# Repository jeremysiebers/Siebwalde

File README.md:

# Siebwalde-Source
Siebwalde project

This project is dedicated for the ModelTrain Yard of Siebwalde: 
- https://www.youtube.com/c/SiebersOrg
- http://www.siebers.org/index.html
- https://www.youtube.com/channel/UCRJYaY8l7wVBrel3Bn0nD2Q/videos?view_as=subscriber

It contains sources for:

Windows Application (C#)

- Siebwalde_Application     --> C# main App to control all

uCOntrollers (C):

- FiddleYard                --> Embedded ethernet uController, controlling the FiddleYard PIC18F97j60

- ServoController.X         --> Embedded uController for RC servo driving

- TrackAmplifier4.X         --> development of track amplifiers; 1 PIC per amplifier (final setup with PIC18F25K40)(PetitModbus)*

- TrackBackplane2.X         --> development of track backplane slave; track amplifier slave select slave for initialization (final setup with PIC18F25K40)(PetitModbus)*

- TrackController5.X        --> development of track controller; PIC32MZ2048EFH144 Ethernet Target + ModBus Master(build upon PetitModbus)*

PCB Files (KiCad):

- KiCad                     --> All Siebwalde related KiCad (PCB) designs

*PetitModbus derived from https://github.com/FxDev/PetitModbus

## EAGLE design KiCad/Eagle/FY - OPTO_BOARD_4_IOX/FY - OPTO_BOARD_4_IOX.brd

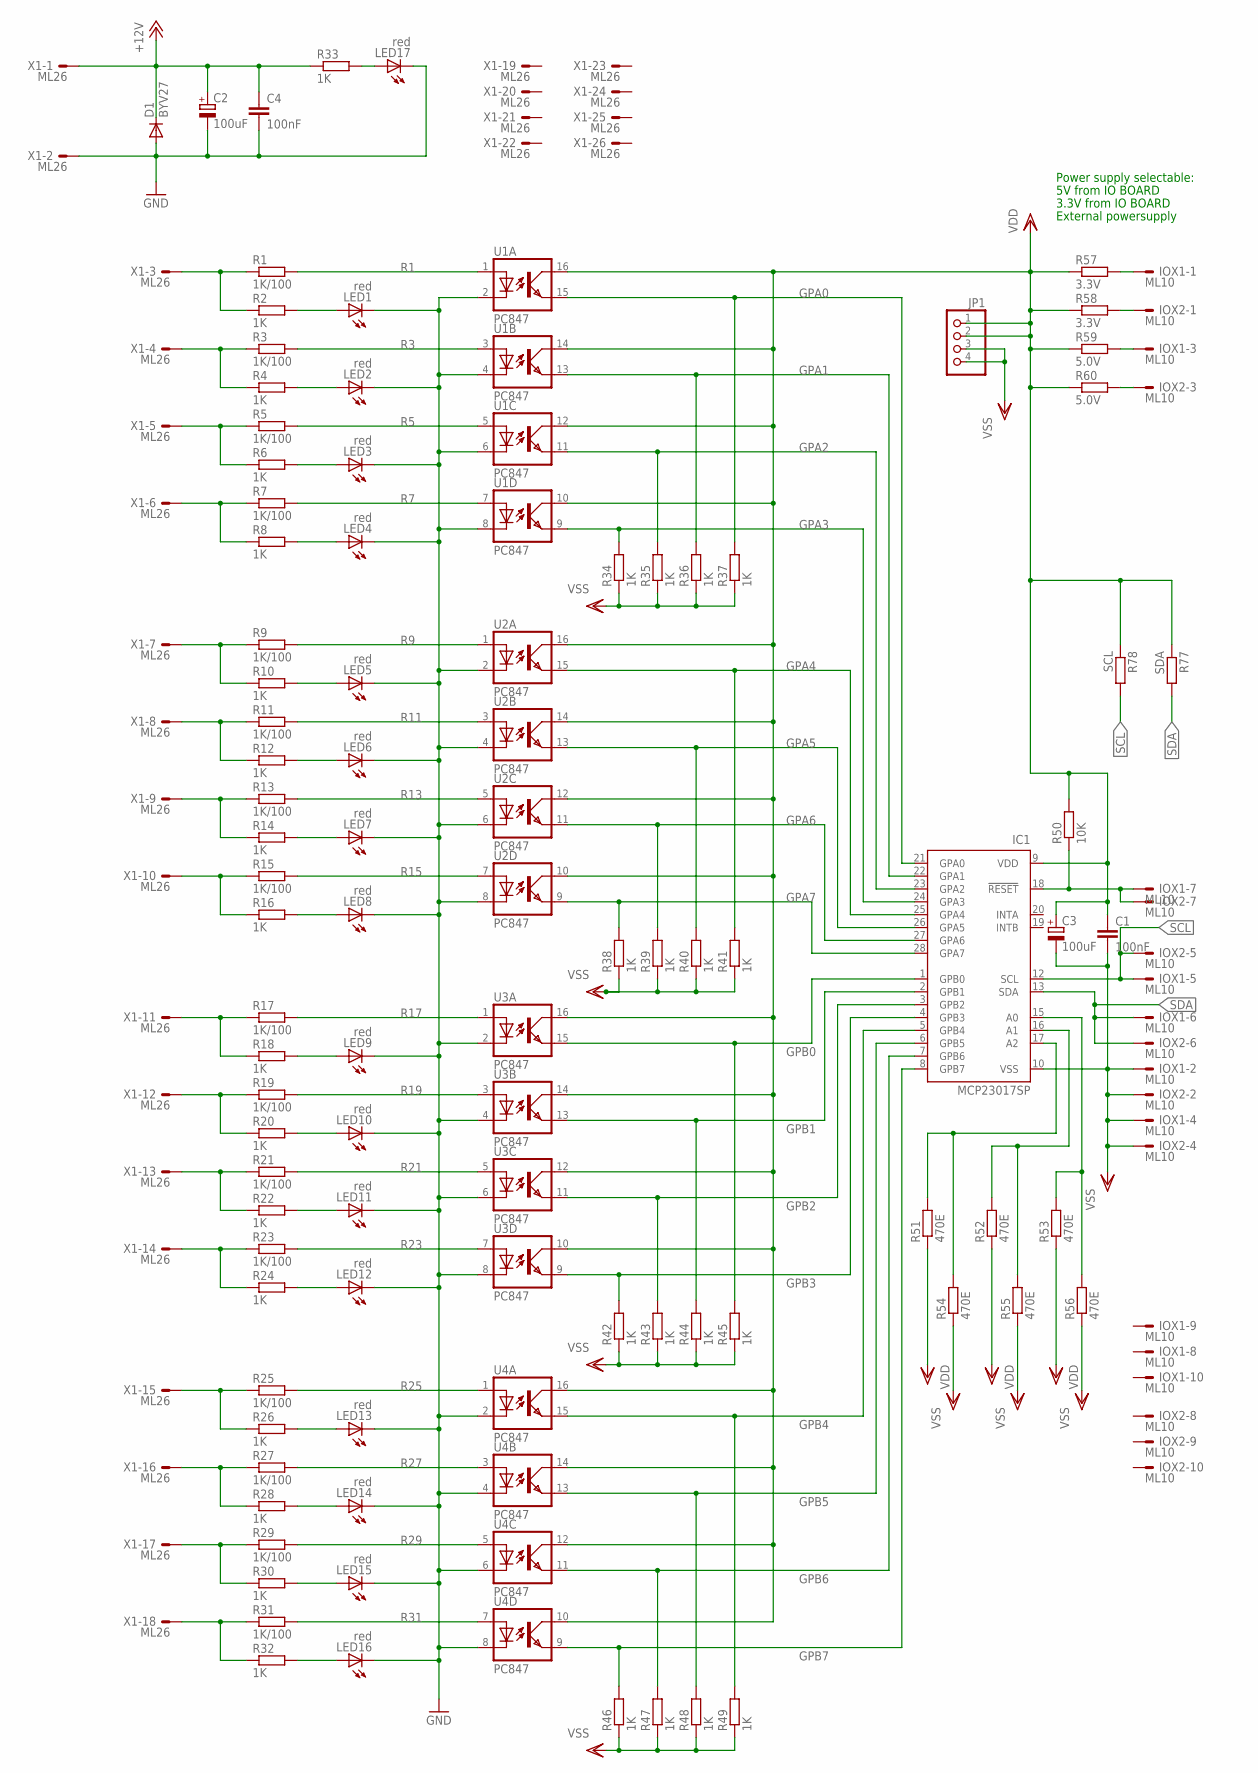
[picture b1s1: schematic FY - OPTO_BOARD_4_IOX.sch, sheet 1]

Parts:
C1, C4: 100nF; C050-025X075
C2, C3: 100uF; E5-8,5
D1: BYV27; SOD57-10
IC1: MCP23017SP; DIL28-3
IOX1, IOX2: ML10
JP1: 1X04
LED1, LED2, LED3, LED4, LED5, LED6, LED7, LED8, LED9, LED10, LED11, LED12, LED13, LED14, LED15, LED16, LED17: red; LED3MM
R1, R3, R5, R7, R9, R11, R13, R15, R17, R19, R21, R23, R25, R27, R29, R31: 1K/100; 0207/10
R2, R4, R6, R8, R10, R12, R14, R16, R18, R20, R22, R24, R26, R28, R30, R32, R33, R34, R35, R36, R37, R38, R39, R40, R41, R42, R43, R44, R45, R46, R47, R48, R49: 1K; 0207/10
R50: 10K; 0207/10
R51, R52, R53, R54, R55, R56: 470E; 0207/10
R57, R58: 3.3V; 0204V
R59, R60: 5.0V; 0204V
R77: SDA; 0207/10
R78: SCL; 0207/10
U1, U2, U3, U4: PC847; DIL16
X1: ML26

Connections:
+12V: C2.+, C4.1, D1.C, R33.1, X1.1; also elsewhere on the board
GND: C2.-, C4.2, D1.A, LED1.K (C), LED2.K (C), LED3.K (C), LED4.K (C), LED5.K (C), LED6.K (C), LED7.K (C), LED8.K (C), LED9.K (C), LED10.K (C), LED11.K (C), LED12.K (C), LED13.K (C), LED14.K (C), LED15.K (C), LED16.K (C), LED17.K (C), U1.2 (C), U1.4 (C), U1.6 (C), U1.8 (C), U2.2 (C), U2.4 (C), U2.6 (C), U2.8 (C), U3.2 (C), U3.4 (C), U3.6 (C), U3.8 (C), U4.2 (C), U4.4 (C), U4.6 (C), U4.8 (C), X1.2
GPA0: IC1.21 (GPA0), R37.2, U1.15 (EMIT); also elsewhere on the board
GPA1: IC1.22 (GPA1), R36.2, U1.13 (EMIT); also elsewhere on the board
GPA2: IC1.23 (GPA2), R35.2, U1.11 (EMIT); also elsewhere on the board
GPA3: IC1.24 (GPA3), R34.2, U1.9 (EMIT); also elsewhere on the board
GPA4: IC1.25 (GPA4), R41.2, U2.15 (EMIT); also elsewhere on the board
GPA5: IC1.26 (GPA5), R40.2, U2.13 (EMIT); also elsewhere on the board
GPA6: IC1.27 (GPA6), R39.2, U2.11 (EMIT); also elsewhere on the board
GPA7: IC1.28 (GPA7), R38.2, U2.9 (EMIT); also elsewhere on the board
GPB0: IC1.1 (GPB0), R45.2, U3.15 (EMIT); also elsewhere on the board
GPB1: IC1.2 (GPB1), R44.2, U3.13 (EMIT); also elsewhere on the board
GPB2: IC1.3 (GPB2), R43.2, U3.11 (EMIT); also elsewhere on the board
GPB3: IC1.4 (GPB3), R42.2, U3.9 (EMIT); also elsewhere on the board
GPB4: IC1.5 (GPB4), R49.2, U4.15 (EMIT); also elsewhere on the board
GPB5: IC1.6 (GPB5), R48.2, U4.13 (EMIT); also elsewhere on the board
GPB6: IC1.7 (GPB6), R47.2, U4.11 (EMIT); also elsewhere on the board
GPB7: IC1.8 (GPB7), R46.2, U4.9 (EMIT); also elsewhere on the board
unnamed: LED1.A, R2.2
unnamed: LED2.A, R4.2
unnamed: LED3.A, R6.2
unnamed: LED4.A, R8.2
unnamed: LED5.A, R10.2
unnamed: LED6.A, R12.2
unnamed: LED7.A, R14.2
unnamed: LED8.A, R16.2
unnamed: LED9.A, R18.2
unnamed: LED10.A, R20.2
unnamed: LED11.A, R22.2
unnamed: LED12.A, R24.2
unnamed: LED13.A, R26.2
unnamed: LED14.A, R28.2
unnamed: LED15.A, R30.2
unnamed: LED16.A, R32.2
unnamed: LED17.A, R33.2
unnamed: IOX1.1, R57.2
unnamed: IOX2.1, R58.2
unnamed: IOX1.3, R59.2
unnamed: IC1.18 (!RESET), IOX1.7, IOX2.7, R50.1
unnamed: IC1.17 (A2), R51.2, R54.2
unnamed: IC1.16 (A1), R52.2, R55.2
unnamed: IC1.15 (A0), R53.2, R56.2
unnamed: IOX2.3, R60.2
R1: R1.2, U1.1 (A); also elsewhere on the board
R3: R3.2, U1.3 (A); also elsewhere on the board
R5: R5.2, U1.5 (A); also elsewhere on the board
R7: R7.2, U1.7 (A); also elsewhere on the board
R9: R9.2, U2.1 (A); also elsewhere on the board
R11: R11.2, U2.3 (A); also elsewhere on the board
R13: R13.2, U2.5 (A); also elsewhere on the board
R15: R15.2, U2.7 (A); also elsewhere on the board
R17: R17.2, U3.1 (A); also elsewhere on the board
R19: R19.2, U3.3 (A); also elsewhere on the board
R21: R21.2, U3.5 (A); also elsewhere on the board
R23: R23.2, U3.7 (A); also elsewhere on the board
R25: R25.2, U4.1 (A); also elsewhere on the board
R27: R27.2, U4.3 (A); also elsewhere on the board
R29: R29.2, U4.5 (A); also elsewhere on the board
R31: R31.2, U4.7 (A); also elsewhere on the board
SCL: IC1.12 (SCL), IOX1.5, IOX2.5, R78.2
SDA: IC1.13 (SDA), IOX1.6, IOX2.6, R77.2
VDD: C1.1, C3.+, IC1.9 (VDD), JP1.1, JP1.2, R50.2, R51.1, R52.1, R53.1, R57.1, R58.1, R59.1, R60.1, R77.1, R78.1, U1.10 (COL), U1.12 (COL), U1.14 (COL), U1.16 (COL), U2.10 (COL), U2.12 (COL), U2.14 (COL), U2.16 (COL), U3.10 (COL), U3.12 (COL), U3.14 (COL), U3.16 (COL), U4.10 (COL), U4.12 (COL), U4.14 (COL), U4.16 (COL)
VSS: C1.2, C3.-, IC1.10 (VSS), IOX1.2, IOX1.4, IOX2.2, IOX2.4, JP1.3, JP1.4, R34.1, R35.1, R36.1, R37.1, R38.1, R39.1, R40.1, R41.1, R42.1, R43.1, R44.1, R45.1, R46.1, R47.1, R48.1, R49.1, R54.1, R55.1, R56.1; also elsewhere on the board
X1-3: R1.1, R2.1, X1.3
X1-4: R3.1, R4.1, X1.4
X1-5: R5.1, R6.1, X1.5
X1-6: R7.1, R8.1, X1.6
X1-7: R9.1, R10.1, X1.7
X1-8: R11.1, R12.1, X1.8
X1-9: R13.1, R14.1, X1.9
X1-10: R15.1, R16.1, X1.10
X1-11: R17.1, R18.1, X1.11
X1-12: R19.1, R20.1, X1.12
X1-13: R21.1, R22.1, X1.13
X1-14: R23.1, R24.1, X1.14
X1-15: R25.1, R26.1, X1.15
X1-16: R27.1, R28.1, X1.16
X1-17: R29.1, R30.1, X1.17
X1-18: R31.1, R32.1, X1.18

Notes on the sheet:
Power supply selectable:
5V from IO BOARD
3.3V from IO BOARD
External powersupply

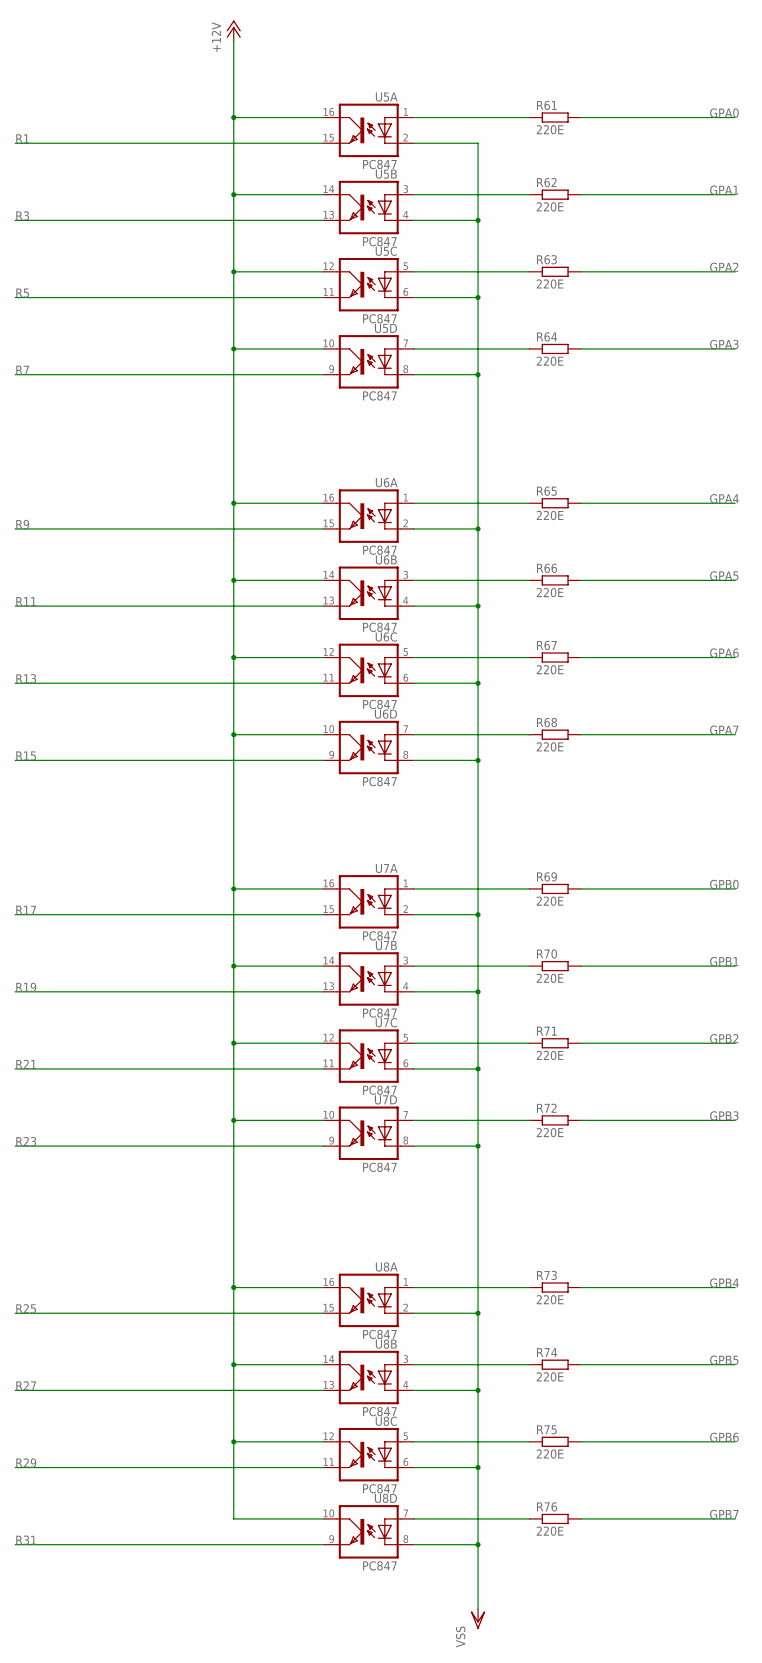
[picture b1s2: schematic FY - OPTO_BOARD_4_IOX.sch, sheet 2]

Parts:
R61, R62, R63, R64, R65, R66, R67, R68, R69, R70, R71, R72, R73, R74, R75, R76: 220E; 0207/10
U5, U6, U7, U8: PC847; DIL16

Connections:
+12V: U5.10 (COL), U5.12 (COL), U5.14 (COL), U5.16 (COL), U6.10 (COL), U6.12 (COL), U6.14 (COL), U6.16 (COL), U7.10 (COL), U7.12 (COL), U7.14 (COL), U7.16 (COL), U8.10 (COL), U8.12 (COL), U8.14 (COL), U8.16 (COL); also elsewhere on the board
GPA0: R61.2; also elsewhere on the board
GPA1: R62.2; also elsewhere on the board
GPA2: R63.2; also elsewhere on the board
GPA3: R64.2; also elsewhere on the board
GPA4: R65.2; also elsewhere on the board
GPA5: R66.2; also elsewhere on the board
GPA6: R67.2; also elsewhere on the board
GPA7: R68.2; also elsewhere on the board
GPB0: R69.2; also elsewhere on the board
GPB1: R70.2; also elsewhere on the board
GPB2: R71.2; also elsewhere on the board
GPB3: R72.2; also elsewhere on the board
GPB4: R73.2; also elsewhere on the board
GPB5: R74.2; also elsewhere on the board
GPB6: R75.2; also elsewhere on the board
GPB7: R76.2; also elsewhere on the board
unnamed: R61.1, U5.1 (A)
unnamed: R62.1, U5.3 (A)
unnamed: R63.1, U5.5 (A)
unnamed: R64.1, U5.7 (A)
unnamed: R65.1, U6.1 (A)
unnamed: R66.1, U6.3 (A)
unnamed: R67.1, U6.5 (A)
unnamed: R68.1, U6.7 (A)
unnamed: R69.1, U7.1 (A)
unnamed: R70.1, U7.3 (A)
unnamed: R71.1, U7.5 (A)
unnamed: R72.1, U7.7 (A)
unnamed: R73.1, U8.1 (A)
unnamed: R74.1, U8.3 (A)
unnamed: R75.1, U8.5 (A)
unnamed: R76.1, U8.7 (A)
R1: U5.15 (EMIT); also elsewhere on the board
R3: U5.13 (EMIT); also elsewhere on the board
R5: U5.11 (EMIT); also elsewhere on the board
R7: U5.9 (EMIT); also elsewhere on the board
R9: U6.15 (EMIT); also elsewhere on the board
R11: U6.13 (EMIT); also elsewhere on the board
R13: U6.11 (EMIT); also elsewhere on the board
R15: U6.9 (EMIT); also elsewhere on the board
R17: U7.15 (EMIT); also elsewhere on the board
R19: U7.13 (EMIT); also elsewhere on the board
R21: U7.11 (EMIT); also elsewhere on the board
R23: U7.9 (EMIT); also elsewhere on the board
R25: U8.15 (EMIT); also elsewhere on the board
R27: U8.13 (EMIT); also elsewhere on the board
R29: U8.11 (EMIT); also elsewhere on the board
R31: U8.9 (EMIT); also elsewhere on the board
VSS: U5.2 (C), U5.4 (C), U5.6 (C), U5.8 (C), U6.2 (C), U6.4 (C), U6.6 (C), U6.8 (C), U7.2 (C), U7.4 (C), U7.6 (C), U7.8 (C), U8.2 (C), U8.4 (C), U8.6 (C), U8.8 (C); also elsewhere on the board

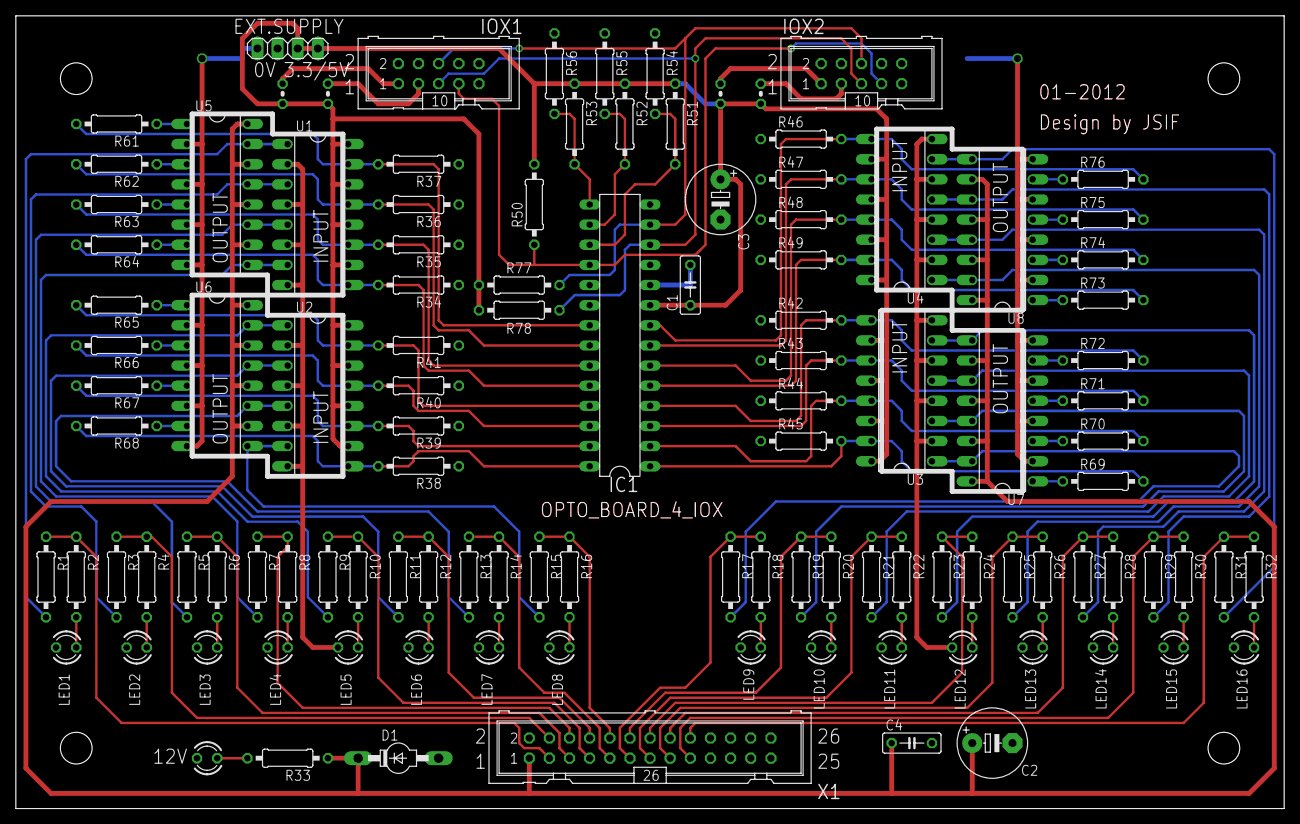
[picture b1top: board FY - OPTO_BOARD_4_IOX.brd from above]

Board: 2 copper layers, 160.0 x 100.0 mm, 113 parts (0 on the bottom side), 95 nets.

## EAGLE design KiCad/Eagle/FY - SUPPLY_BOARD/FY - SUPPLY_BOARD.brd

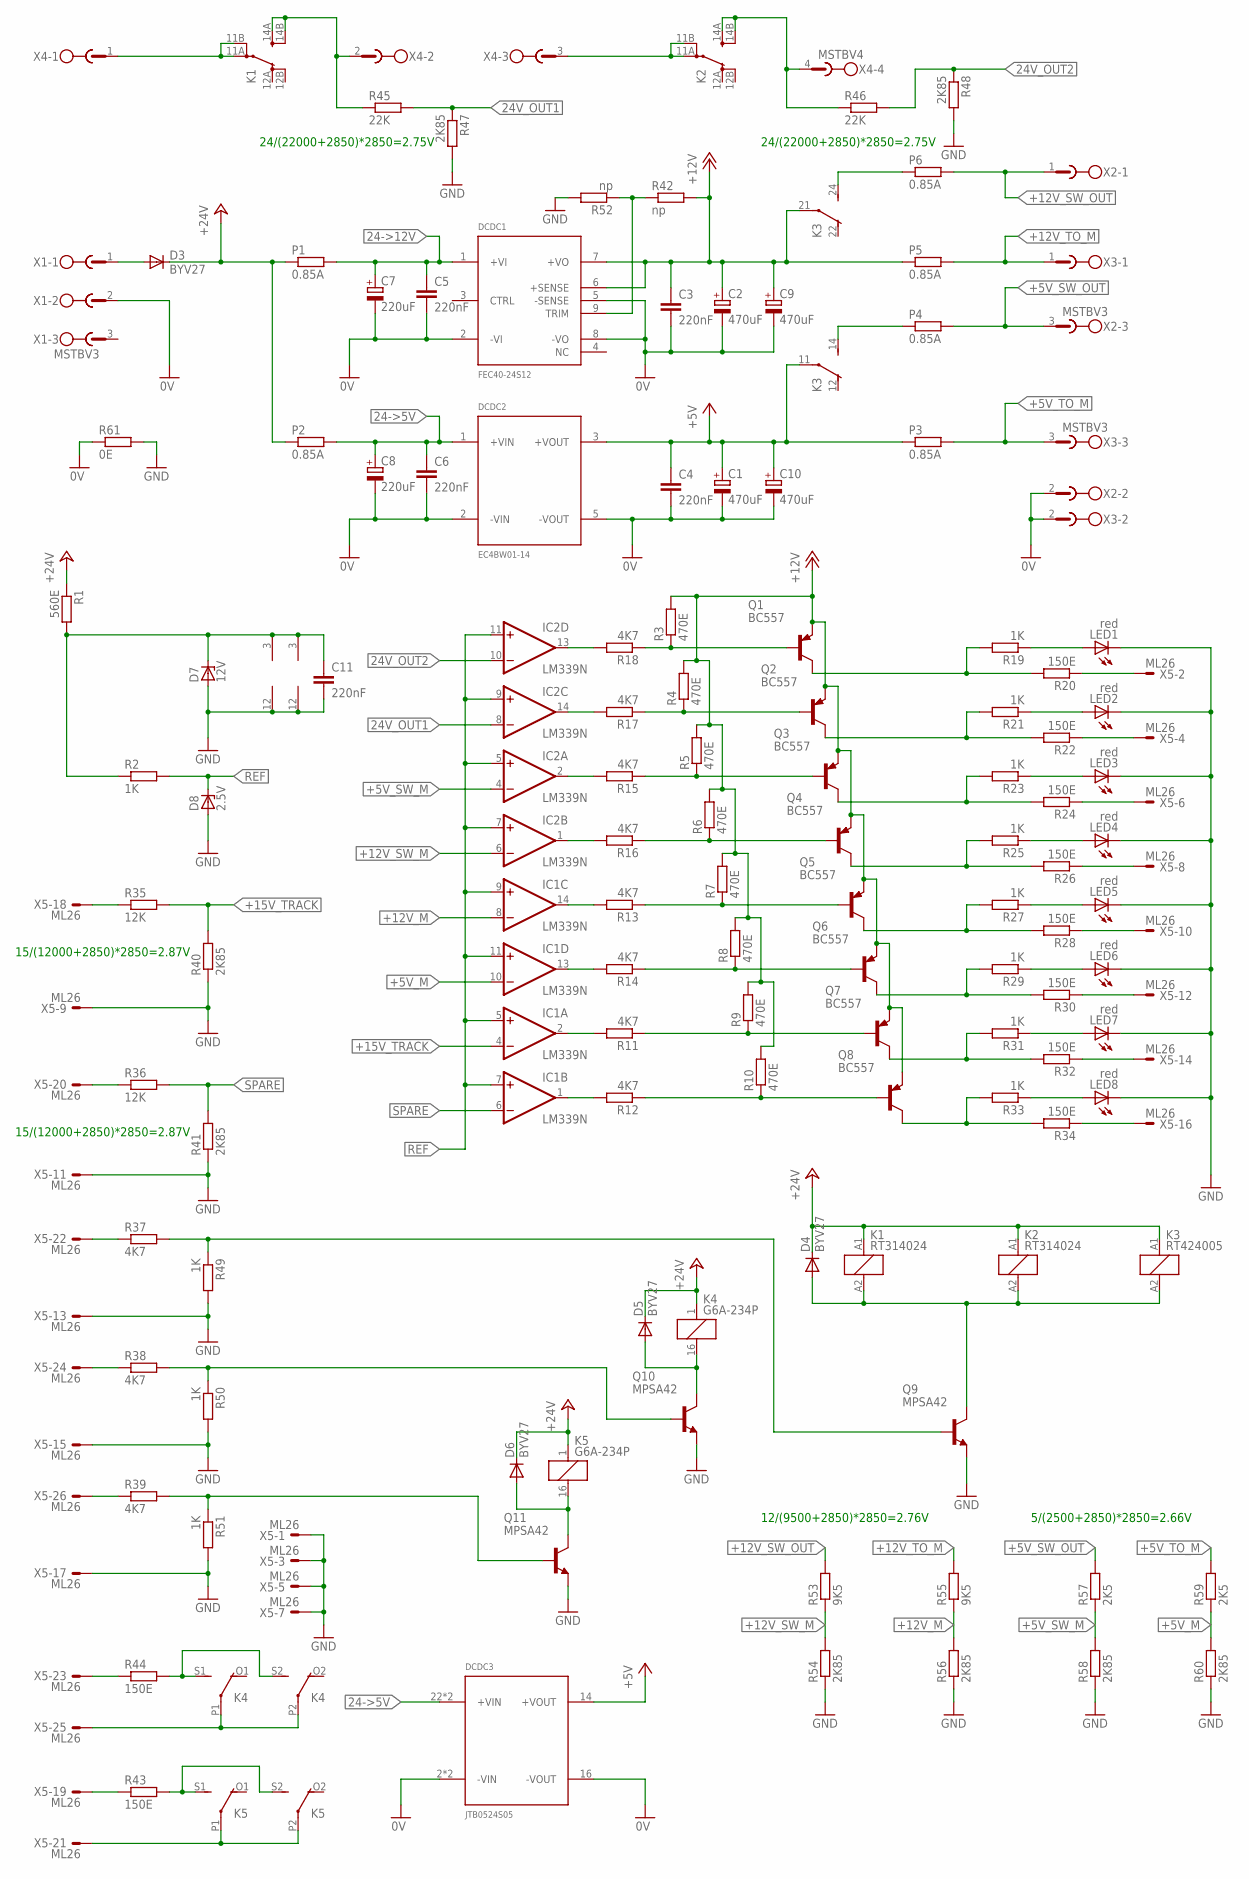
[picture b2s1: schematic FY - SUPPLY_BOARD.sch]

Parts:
C1, C2, C9, C10: 470uF; E5-10,5
C3, C4, C5, C6, C11: 220nF; C050-025X075
C7, C8: 220uF; E5-10,5
D3, D4, D5, D6: BYV27; SOD57-10
D7: 12V; ZDIO-7.5
D8: 2.5V; ZDIO-7.5
DCDC1: FEC40-24S12
DCDC2: EC4BW01-14
DCDC3: JTB0524S05; XP_POWER_5W
IC1, IC2: LM339N; DIL14
K1, K2: RT314024; RT-C/O16A5
K3: RT424005; RT2C/O
K4, K5: G6A-234P
LED1, LED2, LED3, LED4, LED5, LED6, LED7, LED8: red; LED3MM
P1, P2, P3, P4, P5, P6: 0.85A; 0207/7
Q1, Q2, Q3, Q4, Q5, Q6, Q7, Q8: BC557; TO92-EBC
Q9, Q10, Q11: MPSA42; TO92-CBE
R1: 560E; 0411/15
R2, R19, R21, R23, R25, R27, R29, R31, R33, R49, R50, R51: 1K; 0207/10
R3, R4, R5, R6, R7, R8, R9, R10: 470E; 0207/10
R11, R12, R13, R14, R15, R16, R17, R18, R37, R38, R39: 4K7; 0207/10
R20, R22, R24, R26, R28, R30, R32, R34: 150E; 0207/10
R35, R36: 12K; 0207/10
R40, R41, R47, R48, R54, R56, R58, R60: 2K85; 0207/10
R42, R52: np; 0207/10
R43, R44: 150E; 0922/11
R45, R46: 22K; 0207/10
R53, R55: 9K5; 0207/10
R57, R59: 2K5; 0207/10
R61: 0E; 0204V
X1, X2, X3: MSTBV3
X4: MSTBV4
X5: ML26

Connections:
0V: C1.-, C2.-, C3.2, C4.2, C5.2, C6.2, C7.-, C8.-, C9.-, C10.-, DCDC1.2 (-VI), DCDC1.5 (-SENSE), DCDC1.8 (-VO), DCDC2.2 (-VIN), DCDC2.5 (-VOUT), DCDC3.2 (-VIN), DCDC3.3 (-VIN), DCDC3.16 (-VOUT), R61.1, X1.2, X2.2, X3.2
24->5V: C6.1, C8.+, DCDC2.1 (+VIN), DCDC3.22 (+VIN), DCDC3.23 (+VIN), P2.2
24->12V: C5.1, C7.+, DCDC1.1 (+VI), P1.2
24V_OUT1: IC2.8 (-IN), R45.2, R47.1
24V_OUT2: IC2.10 (-IN), R46.2, R48.1
+5V: C1.+, C4.1, C10.+, DCDC2.3 (+VOUT), DCDC3.14 (+VOUT), K3.11, P3.1
+5V_M: IC1.10 (-IN), R59.1, R60.2
+5V_SW_M: IC2.4 (-IN), R57.1, R58.2
+5V_SW_OUT: P4.2, R57.2, X2.3
+5V_TO_M: P3.2, R59.2, X3.3
+12V: C2.+, C3.1, C9.+, DCDC1.6 (+SENSE), DCDC1.7 (+VO), K3.21, P5.1, Q1.E, Q2.E, Q3.E, Q4.E, Q5.E, Q6.E, Q7.E, Q8.E, R3.2, R4.2, R5.2, R6.2, R7.2, R8.2, R9.2, R10.2, R42.2
+12V_M: IC1.8 (-IN), R55.1, R56.2
+12V_SW_M: IC2.6 (-IN), R53.1, R54.2
+12V_SW_OUT: P6.2, R53.2, X2.1
+12V_TO_M: P5.2, R55.2, X3.1
+15V_TRACK: IC1.4 (-IN), R35.2, R40.2
+24V: D3.C, D4.C, D5.C, D6.C, K1.A1 (1), K2.A1 (1), K3.A1 (1), K4.1, K5.1, P1.1, P2.1, R1.1
GND: C11.2, D7.A, D8.A, IC1.12 (GND), IC2.12 (GND), LED1.K (C), LED2.K (C), LED3.K (C), LED4.K (C), LED5.K (C), LED6.K (C), LED7.K (C), LED8.K (C), Q9.E, Q10.E, Q11.E, R40.1, R41.1, R47.2, R48.2, R49.2, R50.2, R51.2, R52.2, R54.1, R56.1, R58.1, R60.1, R61.2, X5.1, X5.3, X5.5, X5.7, X5.9, X5.11, X5.13, X5.15, X5.17
unnamed: K1.11A (PA), K1.11B (PB), X4.1
unnamed: Q1.B, R3.1, R18.1
unnamed: K2.11A (PA), K2.11B (PB), X4.3
unnamed: R35.1, X5.18
unnamed: Q2.B, R4.1, R17.1
unnamed: Q3.B, R5.1, R15.1
unnamed: K3.24 (S), P6.1
unnamed: DCDC1.9 (TRIM), R42.1, R52.1
unnamed: K3.14 (S), P4.1
unnamed: D4.A, K1.A2 (2), K2.A2 (2), K3.A2 (2), Q9.C
unnamed: C11.1, D7.C, IC1.3 (V+), IC2.3 (V+), R1.2, R2.1
unnamed: Q4.B, R6.1, R16.1
unnamed: Q5.B, R7.1, R13.1
unnamed: Q6.B, R8.1, R14.1
unnamed: Q7.B, R9.1, R11.1
unnamed: IC1.2 (OUT), R11.2
unnamed: IC1.1 (OUT), R12.2
unnamed: IC1.14 (OUT), R13.2
unnamed: IC1.13 (OUT), R14.2
unnamed: IC2.2 (OUT), R15.2
unnamed: IC2.1 (OUT), R16.2
unnamed: Q1.C, R19.2, R20.2
unnamed: IC2.14 (OUT), R17.2
unnamed: IC2.13 (OUT), R18.2
unnamed: LED1.A, R19.1
unnamed: R20.1, X5.2
unnamed: Q2.C, R21.2, R22.2
unnamed: R22.1, X5.4
unnamed: Q3.C, R23.2, R24.2
unnamed: R24.1, X5.6
unnamed: Q4.C, R25.2, R26.2
unnamed: R26.1, X5.8
unnamed: Q5.C, R27.2, R28.2
unnamed: R28.1, X5.10
unnamed: Q6.C, R29.2, R30.2
unnamed: R30.1, X5.12
unnamed: Q7.C, R31.2, R32.2
unnamed: R32.1, X5.14
unnamed: Q8.C, R33.2, R34.2
unnamed: R34.1, X5.16
unnamed: Q8.B, R10.1, R12.1
unnamed: LED2.A, R21.1
unnamed: LED3.A, R23.1
unnamed: LED4.A, R25.1
unnamed: LED5.A, R27.1
unnamed: LED6.A, R29.1
unnamed: LED7.A, R31.1
unnamed: LED8.A, R33.1
unnamed: Q9.B, R37.2, R49.1
unnamed: Q10.B, R38.2, R50.1
unnamed: R36.1, X5.20
unnamed: Q11.B, R39.2, R51.1
unnamed: R37.1, X5.22
unnamed: K5.S1 (S), K5.S2 (S), R43.2
unnamed: R38.1, X5.24
unnamed: D5.A, K4.16 (2), Q10.C
unnamed: K4.S1 (S), K4.S2 (S), R44.2
unnamed: R39.1, X5.26
unnamed: D6.A, K5.16 (2), Q11.C
unnamed: R44.1, X5.23
unnamed: D3.A, X1.1
unnamed: R43.1, X5.19
unnamed: K4.P1, K4.P2, X5.25
unnamed: K5.P1, K5.P2, X5.21
unnamed: K2.14A (SA), K2.14B (SB), R46.1, X4.4
unnamed: K1.14A (SA), K1.14B (SB), R45.1, X4.2
REF: D8.C, IC1.5 (+IN), IC1.7 (+IN), IC1.9 (+IN), IC1.11 (+IN), IC2.5 (+IN), IC2.7 (+IN), IC2.9 (+IN), IC2.11 (+IN), R2.2
SPARE: IC1.6 (-IN), R36.2, R41.2

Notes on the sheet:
24/(22000+2850)*2850=2.75V
15/(12000+2850)*2850=2.87V
12/(9500+2850)*2850=2.76V
5/(2500+2850)*2850=2.66V

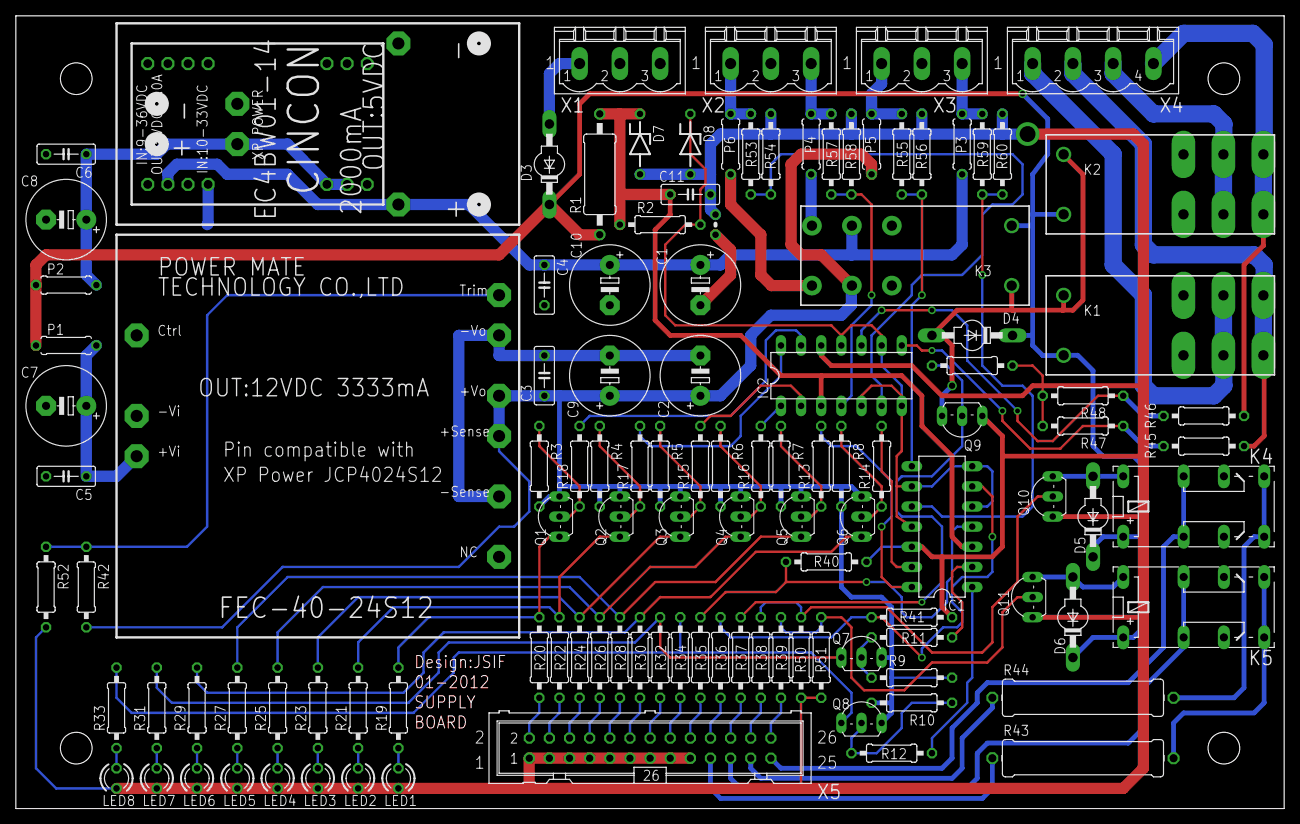
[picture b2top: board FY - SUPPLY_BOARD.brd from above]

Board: 2 copper layers, 160.0 x 100.0 mm, 118 parts (0 on the bottom side), 86 nets.

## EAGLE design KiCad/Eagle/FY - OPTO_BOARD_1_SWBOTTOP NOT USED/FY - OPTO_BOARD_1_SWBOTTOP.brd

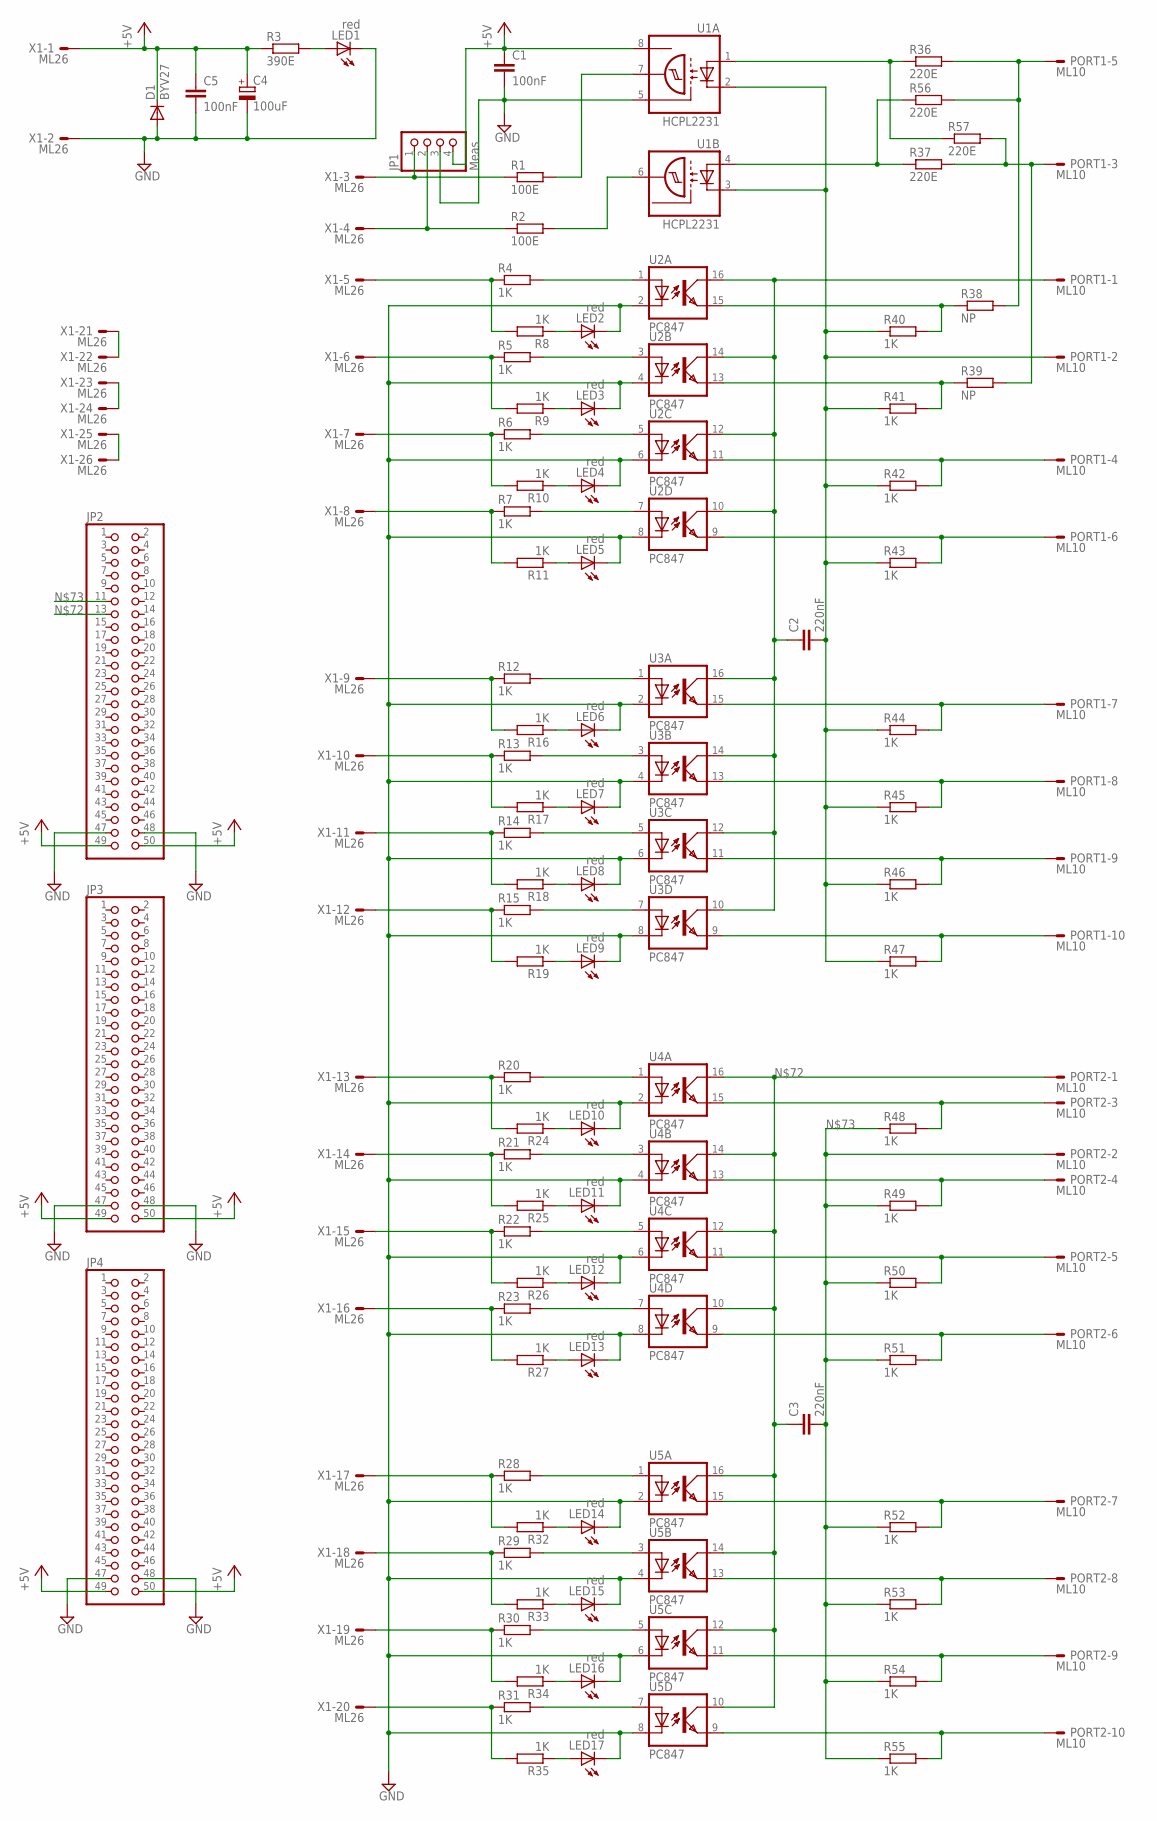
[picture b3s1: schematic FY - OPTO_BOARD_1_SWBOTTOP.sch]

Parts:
C1, C5: 100nF; C050-025X075
C2, C3: 220nF; C050-025X075
C4: 100uF; E5-8,5
D1: BYV27; SOD57-10
JP1: Meas; 1X04
JP2, JP3, JP4: PINHD-2X25; 2X25
LED1, LED2, LED3, LED4, LED5, LED6, LED7, LED8, LED9, LED10, LED11, LED12, LED13, LED14, LED15, LED16, LED17: red; LED3MM
PORT1, PORT2: ML10
R1, R2: 100E; 0207/10
R3: 390E; 0207/10
R4, R5, R6, R7, R8, R9, R10, R11, R12, R13, R14, R15, R16, R17, R18, R19, R20, R21, R22, R23, R24, R25, R26, R27, R28, R29, R30, R31, R32, R33, R34, R35, R40, R41, R42, R43, R44, R45, R46, R47, R48, R49, R50, R51, R52, R53, R54, R55: 1K; 0207/10
R36, R37, R56, R57: 220E; 0207/10
R38, R39: NP; 0207/10
U1: HCPL2231; DIL08
U2, U3, U4, U5: PC847; DIL16
X1: ML26

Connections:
+5V: C1.1, C4.+, C5.1, D1.C, JP1.4, JP2.49, JP2.50, JP3.49, JP3.50, JP4.49, JP4.50, R3.1, U1.8 (VCC), X1.1
GND: C1.2, C4.-, C5.2, D1.A, JP1.3, JP2.47, JP2.48, JP3.47, JP3.48, JP4.47, JP4.48, LED1.K (C), LED2.K (C), LED3.K (C), LED4.K (C), LED5.K (C), LED6.K (C), LED7.K (C), LED8.K (C), LED9.K (C), LED10.K (C), LED11.K (C), LED12.K (C), LED13.K (C), LED14.K (C), LED15.K (C), LED16.K (C), LED17.K (C), U1.5 (GND), U2.2 (C), U2.4 (C), U2.6 (C), U2.8 (C), U3.2 (C), U3.4 (C), U3.6 (C), U3.8 (C), U4.2 (C), U4.4 (C), U4.6 (C), U4.8 (C), U5.2 (C), U5.4 (C), U5.6 (C), U5.8 (C), X1.2
unnamed: R1.2, U1.7 (OUT)
unnamed: LED1.A, R3.2
unnamed: R2.2, U1.6 (OUT)
unnamed: JP1.1, R1.1, X1.3
unnamed: JP1.2, R2.1, X1.4
unnamed: R4.2, U2.1 (A)
unnamed: R5.2, U2.3 (A)
unnamed: R6.2, U2.5 (A)
unnamed: R7.2, U2.7 (A)
unnamed: R4.1, R8.2, X1.5
unnamed: LED2.A, R8.1
unnamed: LED3.A, R9.1
unnamed: LED4.A, R10.1
unnamed: LED5.A, R11.1
unnamed: R5.1, R9.2, X1.6
unnamed: R6.1, R10.2, X1.7
unnamed: R7.1, R11.2, X1.8
unnamed: PORT1.6, R43.2, U2.9 (EMIT)
unnamed: PORT1.4, R42.2, U2.11 (EMIT)
unnamed: R39.1, R41.2, U2.13 (EMIT)
unnamed: R38.1, R40.2, U2.15 (EMIT)
unnamed: R12.2, U3.1 (A)
unnamed: R12.1, R16.2, X1.9
unnamed: C2.1, PORT1.1, U2.10 (COL), U2.12 (COL), U2.14 (COL), U2.16 (COL), U3.10 (COL), U3.12 (COL), U3.14 (COL), U3.16 (COL)
unnamed: R13.2, U3.3 (A)
unnamed: R13.1, R17.2, X1.10
unnamed: PORT1.3, R37.2, R39.2, R57.2
unnamed: R14.2, U3.5 (A)
unnamed: R14.1, R18.2, X1.11
unnamed: PORT1.7, R44.2, U3.15 (EMIT)
unnamed: R15.2, U3.7 (A)
unnamed: R15.1, R19.2, X1.12
unnamed: R36.1, R57.1, U1.1 (A)
unnamed: LED6.A, R16.1
unnamed: LED7.A, R17.1
unnamed: LED8.A, R18.1
unnamed: LED9.A, R19.1
unnamed: R20.2, U4.1 (A)
unnamed: R20.1, R24.2, X1.13
unnamed: R37.1, R56.1, U1.4 (A)
unnamed: LED10.A, R24.1
unnamed: R21.2, U4.3 (A)
unnamed: R21.1, R25.2, X1.14
unnamed: PORT1.5, R36.2, R38.2, R56.2
unnamed: R22.2, U4.5 (A)
unnamed: R22.1, R26.2, X1.15
unnamed: PORT1.8, R45.2, U3.13 (EMIT)
unnamed: R23.2, U4.7 (A)
unnamed: R23.1, R27.2, X1.16
unnamed: PORT1.9, R46.2, U3.11 (EMIT)
unnamed: LED13.A, R27.1
unnamed: LED12.A, R26.1
unnamed: LED11.A, R25.1
unnamed: R28.2, U5.1 (A)
unnamed: R28.1, R32.2, X1.17
unnamed: PORT1.10, R47.2, U3.9 (EMIT)
unnamed: R29.2, U5.3 (A)
unnamed: R29.1, R33.2, X1.18
unnamed: C2.2, PORT1.2, R40.1, R41.1, R42.1, R43.1, R44.1, R45.1, R46.1, R47.1, U1.2 (C), U1.3 (C)
unnamed: R30.2, U5.5 (A)
unnamed: R30.1, R34.2, X1.19
unnamed: R31.2, U5.7 (A)
unnamed: R31.1, R35.2, X1.20
unnamed: PORT2.3, R48.2, U4.15 (EMIT)
unnamed: LED14.A, R32.1
unnamed: LED15.A, R33.1
unnamed: LED16.A, R34.1
unnamed: PORT2.4, R49.2, U4.13 (EMIT)
unnamed: LED17.A, R35.1
unnamed: PORT2.5, R50.2, U4.11 (EMIT)
unnamed: PORT2.6, R51.2, U4.9 (EMIT)
unnamed: C3.1, JP2.13, PORT2.1, U4.10 (COL), U4.12 (COL), U4.14 (COL), U4.16 (COL), U5.10 (COL), U5.12 (COL), U5.14 (COL), U5.16 (COL)
unnamed: C3.2, JP2.11, PORT2.2, R48.1, R49.1, R50.1, R51.1, R52.1, R53.1, R54.1, R55.1
unnamed: PORT2.7, R52.2, U5.15 (EMIT)
unnamed: PORT2.8, R53.2, U5.13 (EMIT)
unnamed: PORT2.9, R54.2, U5.11 (EMIT)
unnamed: PORT2.10, R55.2, U5.9 (EMIT)
unnamed: X1.21, X1.22
unnamed: X1.25, X1.26
unnamed: X1.23, X1.24

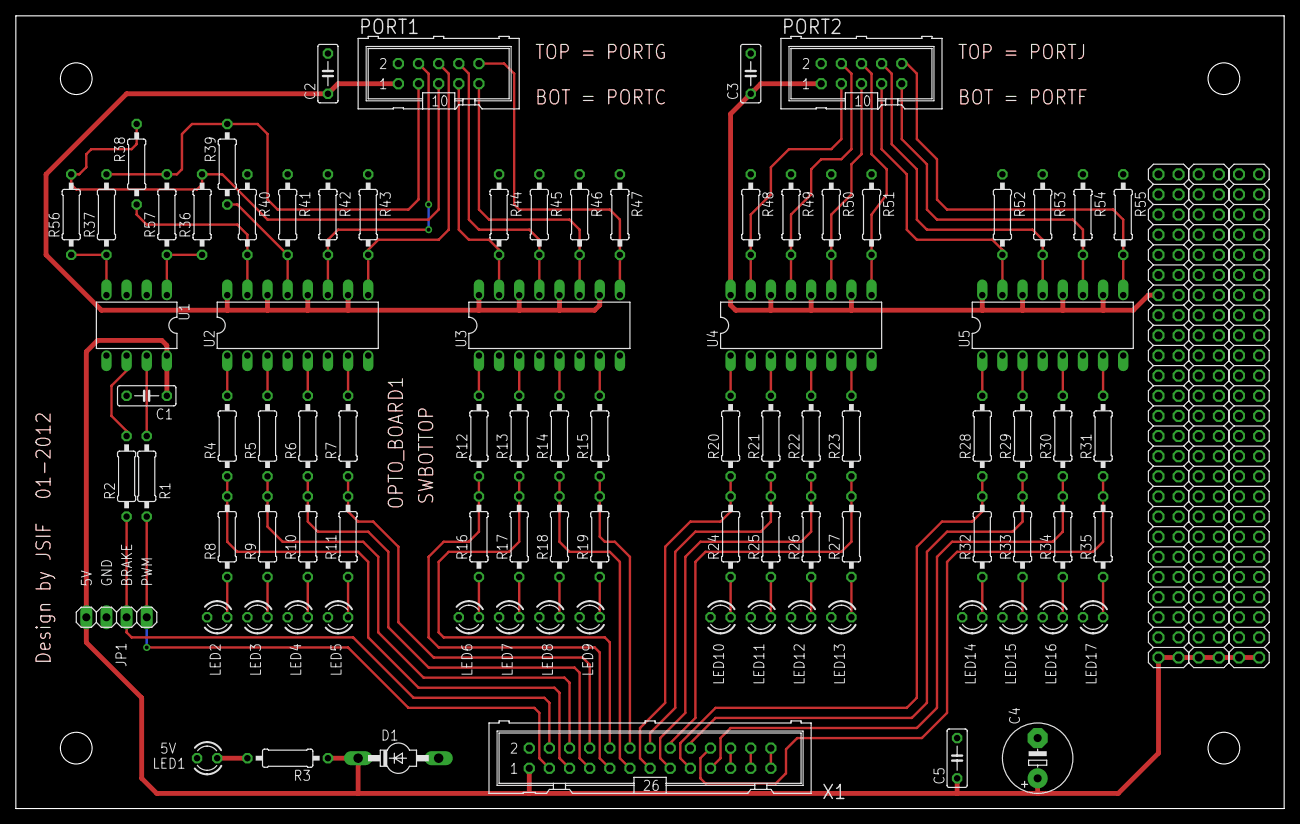
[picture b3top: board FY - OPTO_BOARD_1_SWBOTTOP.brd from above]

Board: 2 copper layers, 160.0 x 100.0 mm, 92 parts (0 on the bottom side), 82 nets.
